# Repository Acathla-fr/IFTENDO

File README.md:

# IFTENDO
Extention to the IFT-C3 board with OLED screen (128x64), I2C address : 0x3C, and buttons

SDA: GPIO5<br>
SCL: GPIO6

Keyboard: <br>
GPIO20 (RX) -> Output 1<br>
GPIO10 -> Output 2<br>
GPIO0  -> Output 3<br>
GPIO7  -> Input 1<br>
GPIO8  -> Input 2<br>
GPIO9  -> Input 3<br>

Up     : O_1, I_1<br>
Left   : O_1, I_2<br>
Down   : O_1, I_3<br>
Right  : O_2, I_1<br>
Select : O_2, I_2<br>
Start  : O_2, I_3<br>
A      : O_3, I_1<br>
B      : O_3, I_2

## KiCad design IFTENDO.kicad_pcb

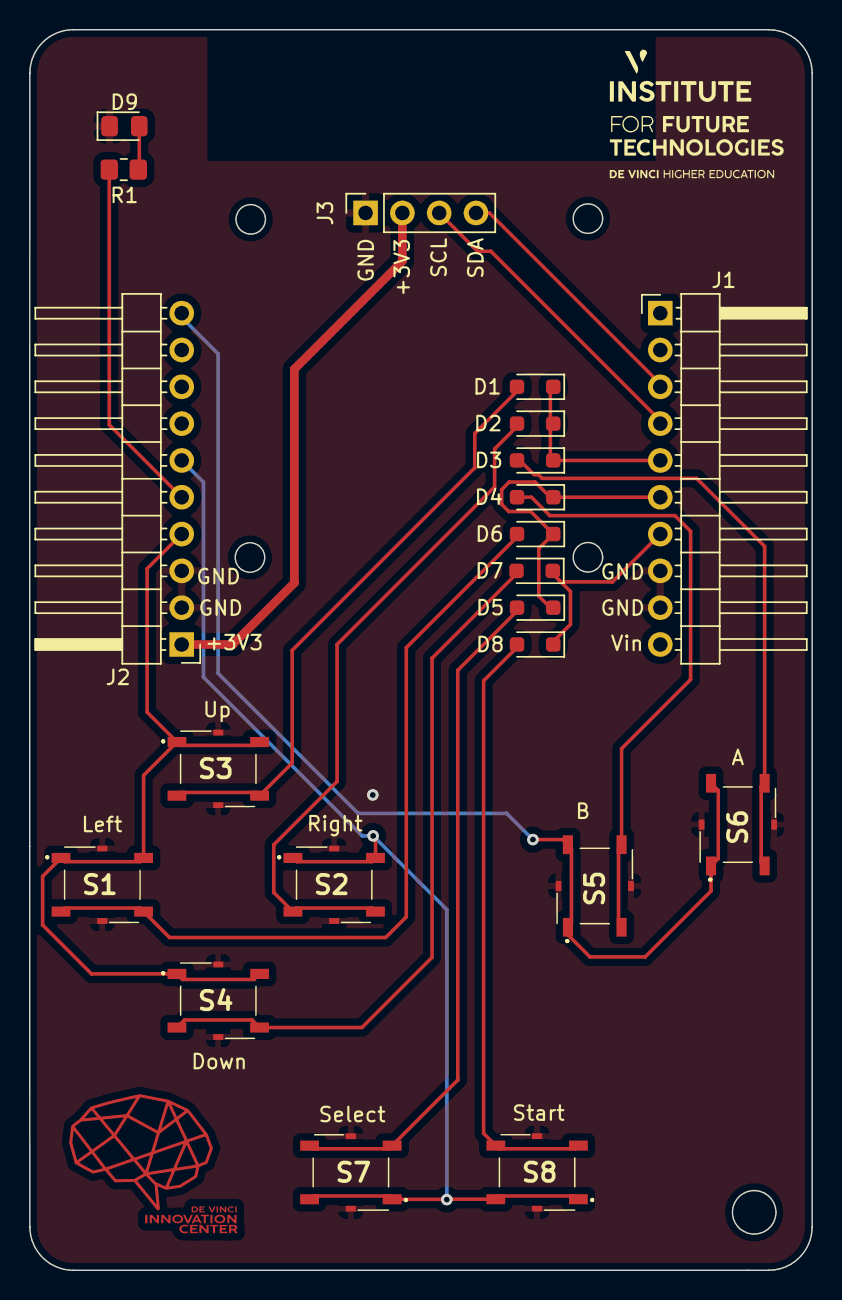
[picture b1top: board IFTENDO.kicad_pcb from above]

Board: 2 copper layers, 54.0 x 85.6 mm, 21 parts (0 on the bottom side), 20 nets.

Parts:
D1, D2, D3, D4, D5, D6, D7, D8: 1N4148WS; D_SOD-323_HandSoldering
D9: LED; D_0805_2012Metric_Pad1.15x1.40mm_HandSolder
J1, J2: Conn_01x10_Pin; PinHeader_1x10_P2.54mm_Horizontal
J3: Conn_01x04_Socket; PinSocket_1x04_P2.54mm_Vertical
R1: 10K; R_0805_2012Metric_Pad1.20x1.40mm_HandSolder
S1, S2, S3, S4, S5, S6, S7, S8: PTS526_SMG15J_SMTR2_LFS; PTS526SMG15JSMTR2LFS

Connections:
+3.3V: J2.1, J3.2
/ButtonA/NO: D3.2 (A), S6.3 (NO_1), S6.4 (NO_2)
/ButtonB/NO: D4.2 (A), S5.3 (NO_1), S5.4 (NO_2)
/ButtonDown/NO: D7.2 (A), S4.3 (NO_1), S4.4 (NO_2)
/ButtonLeft/NO: D6.2 (A), S1.3 (NO_1), S1.4 (NO_2)
/ButtonRight/NO: D2.2 (A), S2.3 (NO_1), S2.4 (NO_2)
/ButtonSelect/NO: D5.2 (A), S7.3 (NO_1), S7.4 (NO_2)
/ButtonStart/NO: D8.2 (A), S8.3 (NO_1), S8.4 (NO_2)
/ButtonUp/NO: D1.2 (A), S3.3 (NO_1), S3.4 (NO_2)
/GPIO0: J2.10, S5.1 (COM_1), S5.2 (COM_2), S6.1 (COM_1), S6.2 (COM_2)
/GPIO5: J1.3, J3.4
/GPIO6: J1.4, J3.3
/GPIO7: D1.1 (K), D2.1 (K), D3.1 (K), J1.5
/GPIO8: D4.1 (K), D5.1 (K), D6.1 (K), J1.6
/GPIO9: D7.1 (K), D8.1 (K), J1.7
/GPIO10: J2.6, S2.1 (COM_1), S2.2 (COM_2), S7.1 (COM_1), S7.2 (COM_2), S8.1 (COM_1), S8.2 (COM_2)
/O_1: J2.4, S1.1 (COM_1), S1.2 (COM_2), S3.1 (COM_1), S3.2 (COM_2), S4.1 (COM_1), S4.2 (COM_2)
/Tx: J2.5, R1.1
GND: D9.1 (K), J1.8, J1.9, J2.2, J2.3, J3.1, S1.5 (GND_1), S1.6 (GND_2), S2.5 (GND_1), S2.6 (GND_2), S3.5 (GND_1), S3.6 (GND_2), S4.5 (GND_1), S4.6 (GND_2), S5.5 (GND_1), S5.6 (GND_2), S6.5 (GND_1), S6.6 (GND_2), S7.5 (GND_1), S7.6 (GND_2), S8.5 (GND_1), S8.6 (GND_2)
unnamed: D9.2 (A), R1.2

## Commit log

2023-11-08 Version sent to aisler for production
2023-11-15 Create README.md
    Pin definitions and button location
2023-11-21 I2C address added
2024-06-06 Tofs
    Images of the PCB from kicad
